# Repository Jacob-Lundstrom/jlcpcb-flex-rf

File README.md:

JLCPCB Flexible PCB RF verification
========================

## Summary and justification 

This experiment was created to suppliment another one of my projects, to verify and ensure that JLCPCB's Flexible PCBs would be sufficient for rudimentary RF boards.
Looking through JLCPCB's stackups, all flexible PCBs have identical substrate thicknesses, and the thicker boards merely change the copper wight and accompanying adhesive/coverlay. 
Because of this, the lightest copper weight was chosen for this Experiment. The copper weight is a significant limitation; for the given polyimide substrate dk that is 
specified by JLCPCB of 3.3 and the minimal distance of 25 um between copper layers, controlled impedance is exceedingly difficult to achieve (See the Trace Calculations section at 
the end of this README).

An additional reason to perform this experiment is to charactarize the effect of the coverlay material (Specified by JLCPCB at 2.9) on RF performance.
For this reason, I have included both coverlay and coverlay-removed sections for both the 2 mil and 3 mil traces.
Furthermore, this board will be used in combination with other materials, specifically an epoxy resin, to measure their respective effects on performance as well.

There are a plethora of stiffener materials which are not accounted for that JLCPCB offers. These materials may be tested in future experiments but are 
not charactarized in this experiment.

The order for the first round of boards was placed on 6/13, and assembly and testing were performed on 6/25.

## Methodology

PCBs were designed using KICAD 7, and manufactured at JLCPCB. The PCBs had the standard 1/3 oz copper stackup JLCPCB offers, as presented below.

Once the PCBs arrived, I hand assembled them, using a stencil and solder paste along side a hot plate set to a temperature of 300 degrees Celsius. The hand-placed SMA connectors may have less than ideal 
connections.

Within the PCB layout, the sections were split up into 8 lanes, with each lane having some small change between each of them. The following parameters were varied between each lane:
- Trace thickness (2mil/3mil)
- Load element type (50 Ohm Load/Chip Antenna)
- Coverlay (Present/Absent)

All data was collected using a LiteVNA, calibrated with the provided calibration standard in the kit at the end of coaxial cables. The cal standards were then removed, and measurments commenced.

For all measurments, the PCBs were placed on a rubber ESD safe mat over a wood bench. Measurements were taken with port 1 of the VNA connecting to the SMA connector furthest from the load element, and 
port 2 connecting to the corresponding SMA closest to the load element.

## Results

From the collected data, it appears that the flexible PCB stackup offered by JLCPCB is insufficient in allowing for proper RF transmission over large distances.
As shown in the preview images, as the frequency of the incident wave increases, the reflection coefficient approaches 1. This causes extremely poor if not zero RF signal
transmission to a load. The observed and presented result was nearly uniform between all trial lanes, with identical data between the two assembled boards.

It is for this purpose that if any RF signals are to be present on a flexible PCB of this stackup, the conducting traces should be kept as short as possible to minimize the effect
of the charactaristic impedance. Traces should therefore follow the rule of thumb to keep total track length a distance of less 1/10th the wavelength of the active frequency.

Additionally, the presence of flesh (bringing my hand closer to the board) resulted with small but noticeable affects; this may indicate that the RF ring project that I'm working on
may be feasible as no significant effects were observed. However, with the additional results indicating poor RF performance in absence of my hand, it may be that it is doomed to fail.

The additional material planned to be tested has not been selected; I am currently in the process of finding a viable epoxy resin to use in the final implementation for the aforementioned
ring project.

## Trace calculations

For a nominal impedance of 50 Ohms, and a copper weight of 0.33 oz, a trace thickness of 1.5411 mils is required as per IPC 2141 specifications.

JLCPCB's manufacturing limiations require an absolute minimum trace width of 2 mils, with a recommendataion to stay as far away from 2 mils as possible. 
Again following the IPC 2141 calculations, this yields a charactaristic impedance of 42.11 Ohms. This gives a decent VSWR of 1.187, which should be sufficient for short
distance RF signal transmission.

JLCPCB recommends limitation to 3 mil trace widths.
The downside of the larger trace widths is a lower charactaristic impedance and therefore a higher VSWR. 
However, this provides the benefit of manufacturing consistency. It may be more desireable to have guaranteed manufacturability
at the cost of worse performance. This test is aimed at verifying this too. 

Per the IPC 2141 calculations, a 3 mil trace width gives a charactaristic impedance of 28.93 Ohms, and therefore an ideal VSWR of 1.728. 
This performance is much worse, but may just suffice in extremely short distance communication.

Larger copper thickness require proportionally thinner traces, which becomes impossible to manufacture, especially with the 1 oz copper weight. Therefore, if one
hopes to use flexible PCBs with controlled impedances, only the 0.33 oz copper option should be used.
Shown below are the 0.12 mm and 0.2 mm trace thickness calculations respectively.

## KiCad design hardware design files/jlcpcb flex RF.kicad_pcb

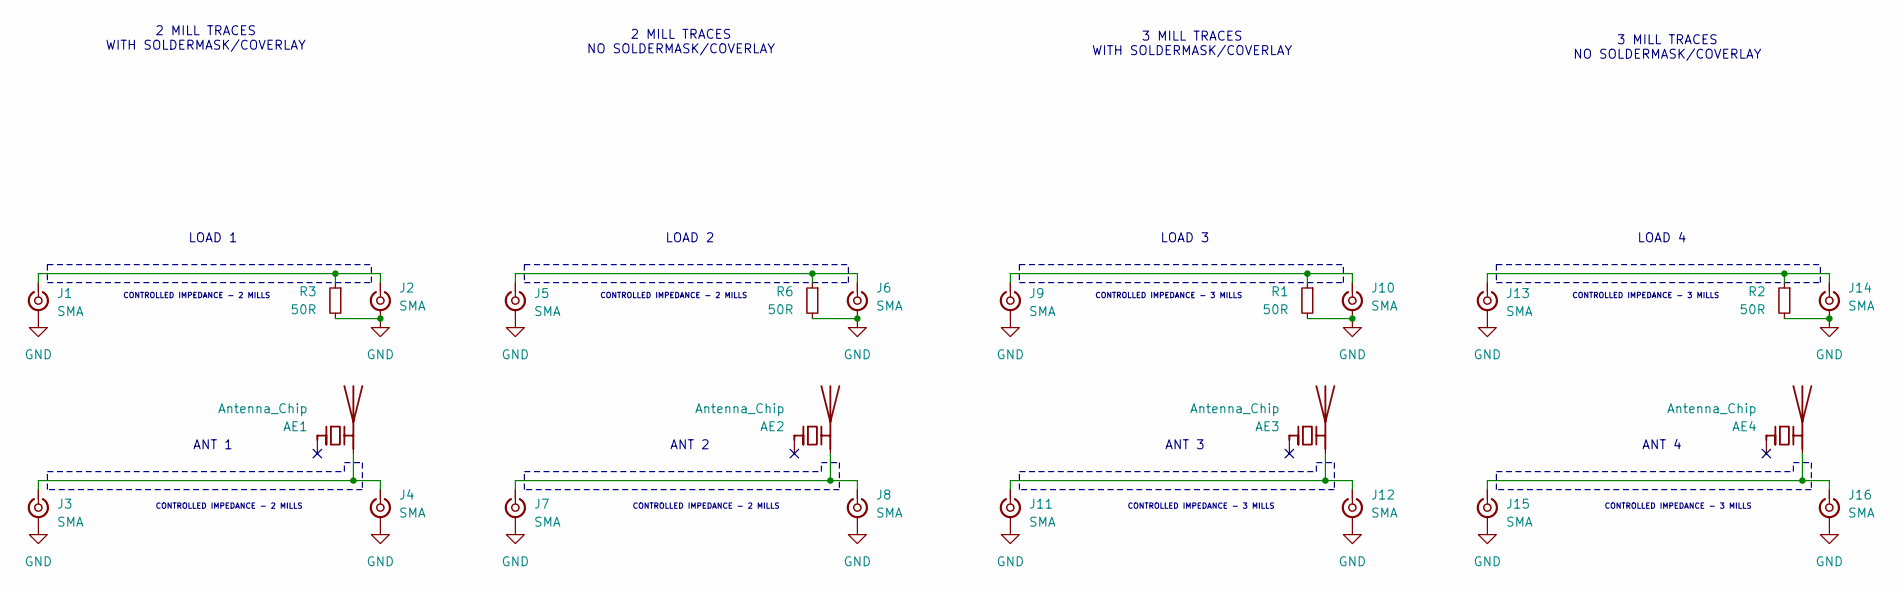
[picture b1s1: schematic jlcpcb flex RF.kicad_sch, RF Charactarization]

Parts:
AE1, AE2, AE3, AE4: Antenna_Chip; Johanson_2450AT18x100
J1, J2, J3, J4, J5, J6, J7, J8, J9, J10, J11, J12, J13, J14, J15, J16: SMA; SMA_Amphenol_132134-10_Vertical
R1, R2, R3, R6: 50R; R_0402_1005Metric

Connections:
GND: J1.2 (Ext), J2.2 (Ext), J3.2 (Ext), J4.2 (Ext), J5.2 (Ext), J6.2 (Ext), J7.2 (Ext), J8.2 (Ext), J9.2 (Ext), J10.2 (Ext), J11.2 (Ext), J12.2 (Ext), J13.2 (Ext), J14.2 (Ext), J15.2 (Ext), J16.2 (Ext), R1.2, R2.2, R3.2, R6.2
unnamed: AE1.2 (PCB_Trace), J3.1 (In), J4.1 (In)
unnamed: AE2.2 (PCB_Trace), J7.1 (In), J8.1 (In)
unnamed: AE3.2 (PCB_Trace), J11.1 (In), J12.1 (In)
unnamed: AE4.2 (PCB_Trace), J15.1 (In), J16.1 (In)
unnamed: J1.1 (In), J2.1 (In), R3.1
unnamed: J5.1 (In), J6.1 (In), R6.1
unnamed: J9.1 (In), J10.1 (In), R1.1
unnamed: J13.1 (In), J14.1 (In), R2.1

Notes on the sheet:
LOAD 4
ANT 4
LOAD 1
CONTROLLED IMPEDANCE - 2 MILLS
ANT 1
3 MILL TRACES NO SOLDERMASK/COVERLAY
3 MILL TRACES WITH SOLDERMASK/COVERLAY
CONTROLLED IMPEDANCE - 3 MILLS
2 MILL TRACES NO SOLDERMASK/COVERLAY
ANT 2
ANT 3
2 MILL TRACES WITH SOLDERMASK/COVERLAY
LOAD 3
LOAD 2

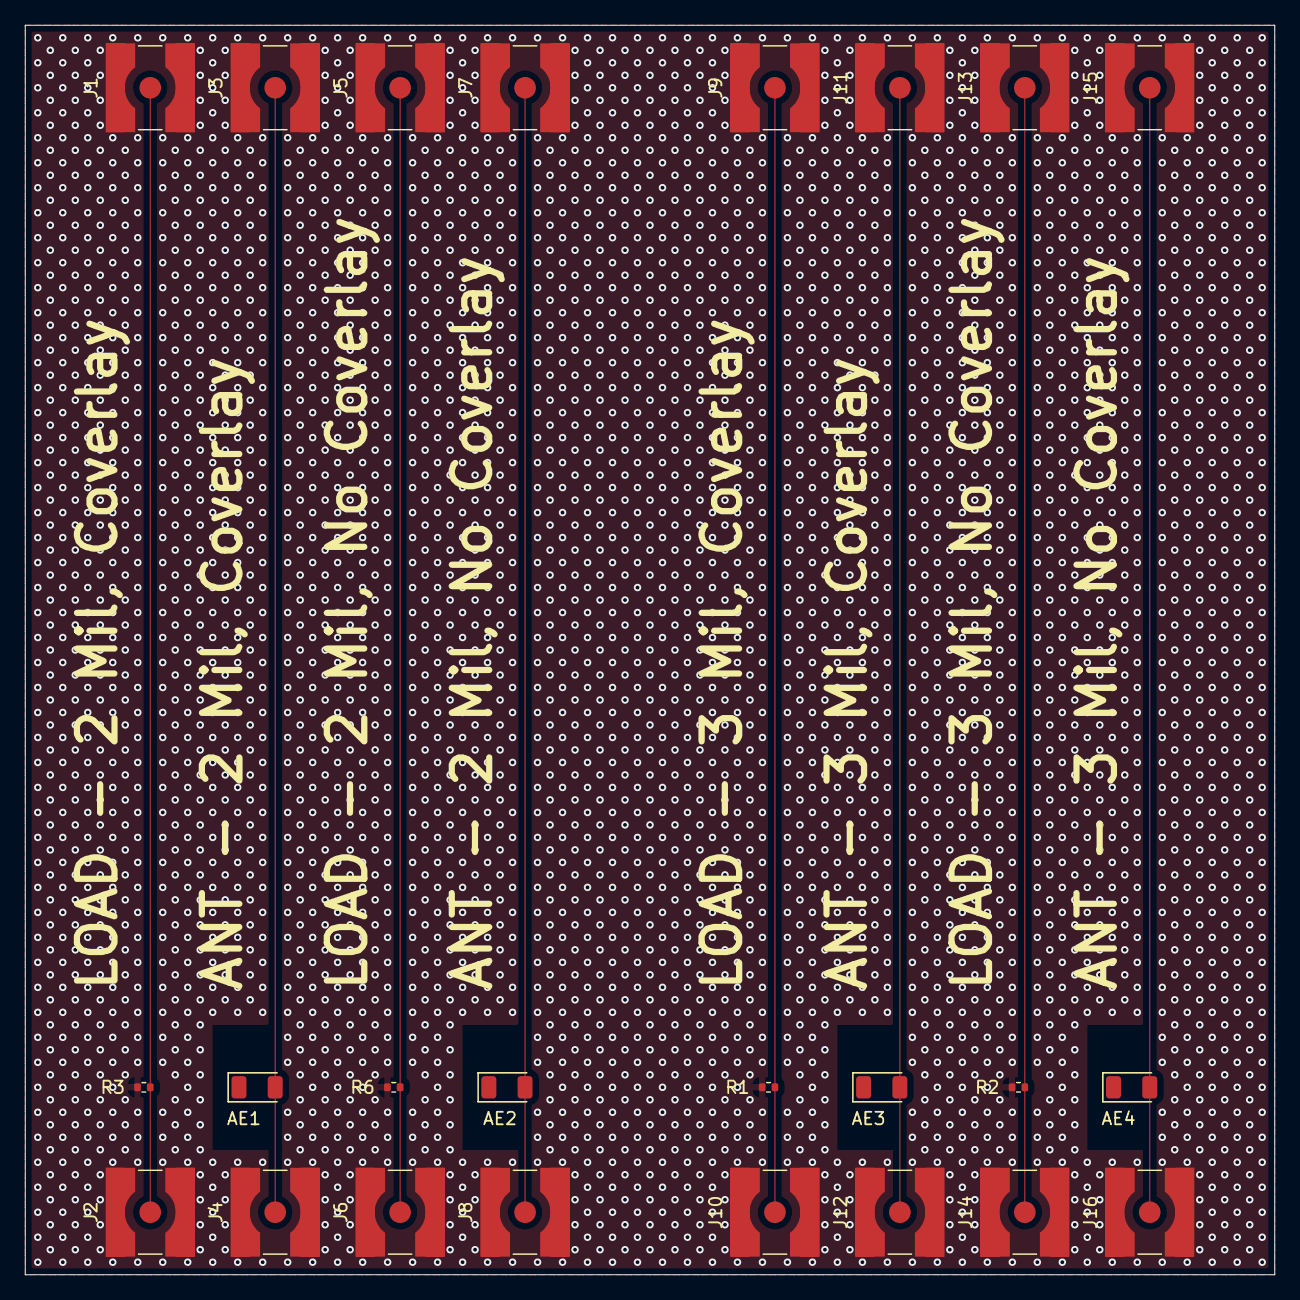
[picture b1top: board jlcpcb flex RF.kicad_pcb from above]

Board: 2 copper layers, 100.0 x 100.0 mm, 24 parts (0 on the bottom side), 9 nets.

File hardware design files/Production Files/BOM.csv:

Reference,Value,Datasheet,Footprint,Qty,Digikey PN
"AE1,AE2,AE3,AE4",Antenna_Chip,~,RF_Antenna:Johanson_2450AT18x100,4,712-2450AT18A0100001ECT-ND
"J1,J2,J3,J4,J5,J6,J7,J8,J9,J10,J11,J12,J13,J14,J15,J16",SMA,~,Connector_Coaxial:SMA_Amphenol_132134-10_Vertical,16,J819-ND
"R1,R2,R3,R6",50R,~,Resistor_SMD:R_0402_1005Metric,4,13-RT0402BRE0750RLCT-ND

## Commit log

2024-06-14 Hardware Files
2024-06-14 Trace impedance calculations
2024-06-14 Schematic Labeling
2024-06-14 Design File Reorganizing
2024-06-14 Antenna Ground Plane Openings
2024-06-16 Larger coverlay removal for manufacturability
2024-06-26 Board 1 Data collection
2024-06-26 Additional readme images
2024-07-13 Qucs Simulation results
2024-07-13 Qucs corrections
